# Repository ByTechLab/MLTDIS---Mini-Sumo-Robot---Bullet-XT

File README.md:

<div align="center">
    
</div>

Mini sumo robot - Bullet XT.

### Read more at BYTECHLAB:

<table style="width: 100%; border: none;" cellspacing="0" cellpadding="0" border="0">
  <tr>
    <td></td>
    <td>https://bytechlab.com/2017/09/minisumo-bullet-xt/</td>
  </tr>
</table>

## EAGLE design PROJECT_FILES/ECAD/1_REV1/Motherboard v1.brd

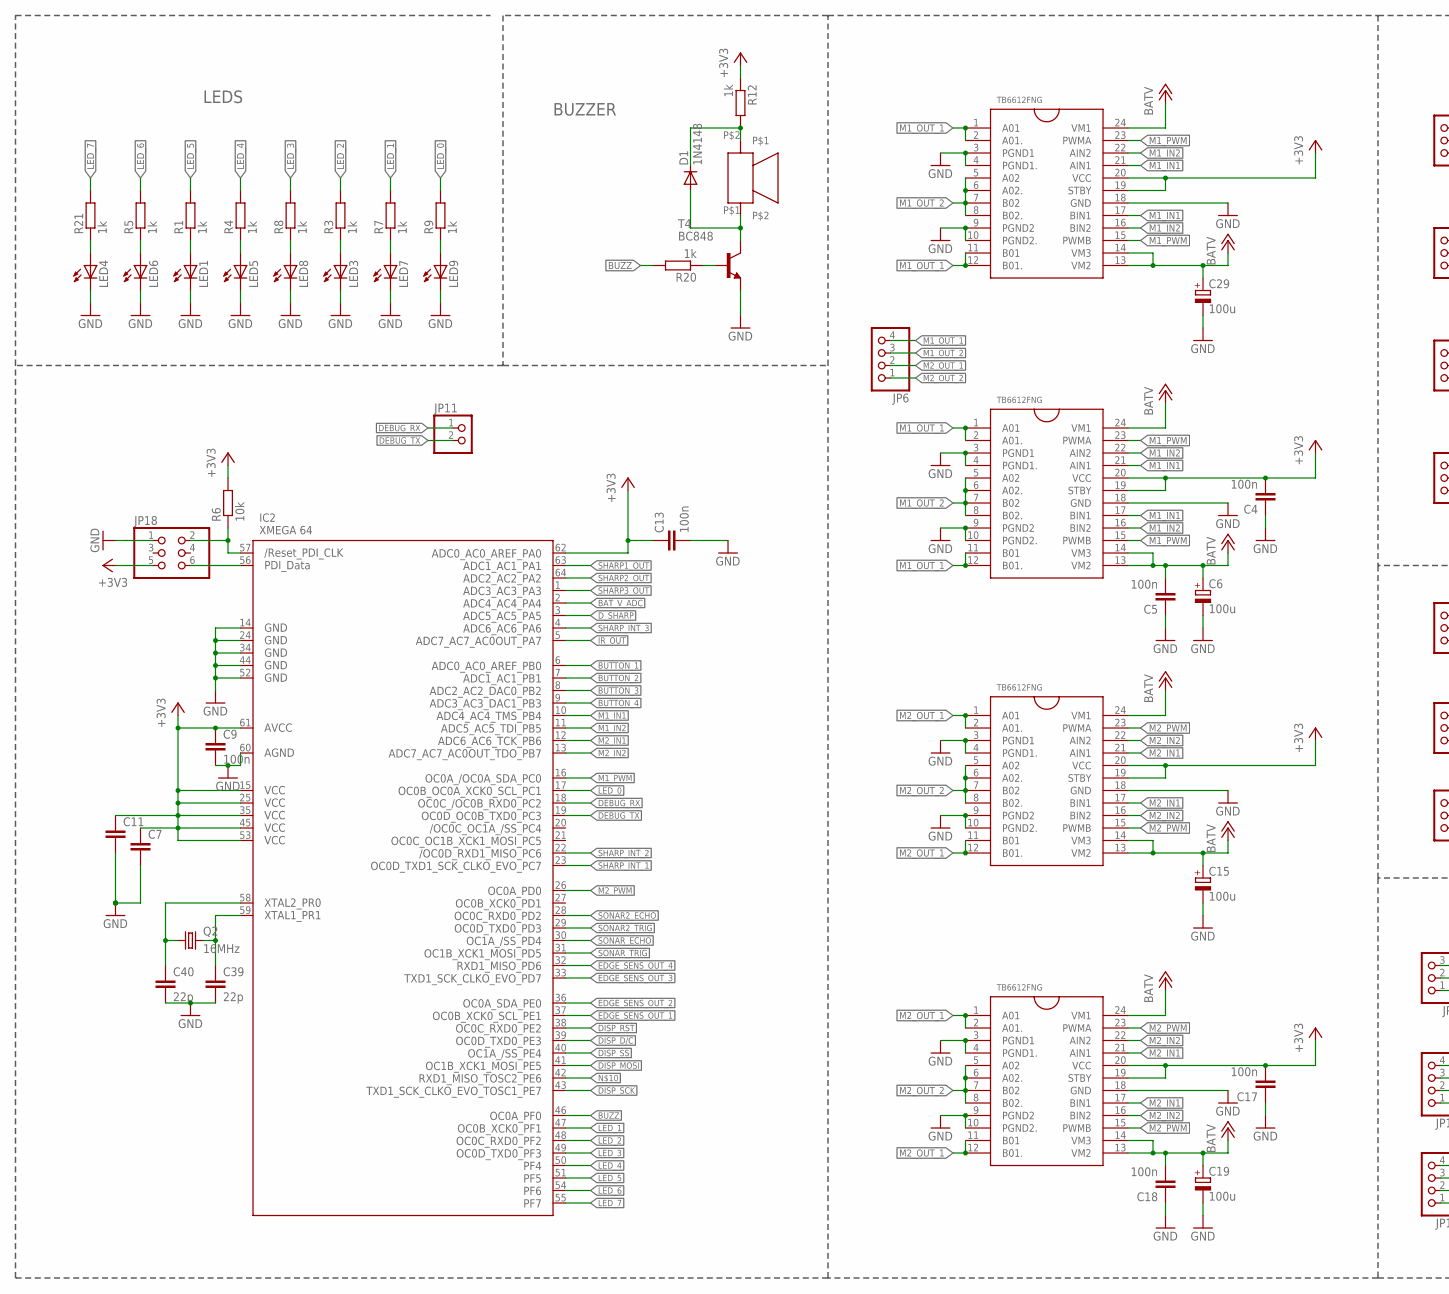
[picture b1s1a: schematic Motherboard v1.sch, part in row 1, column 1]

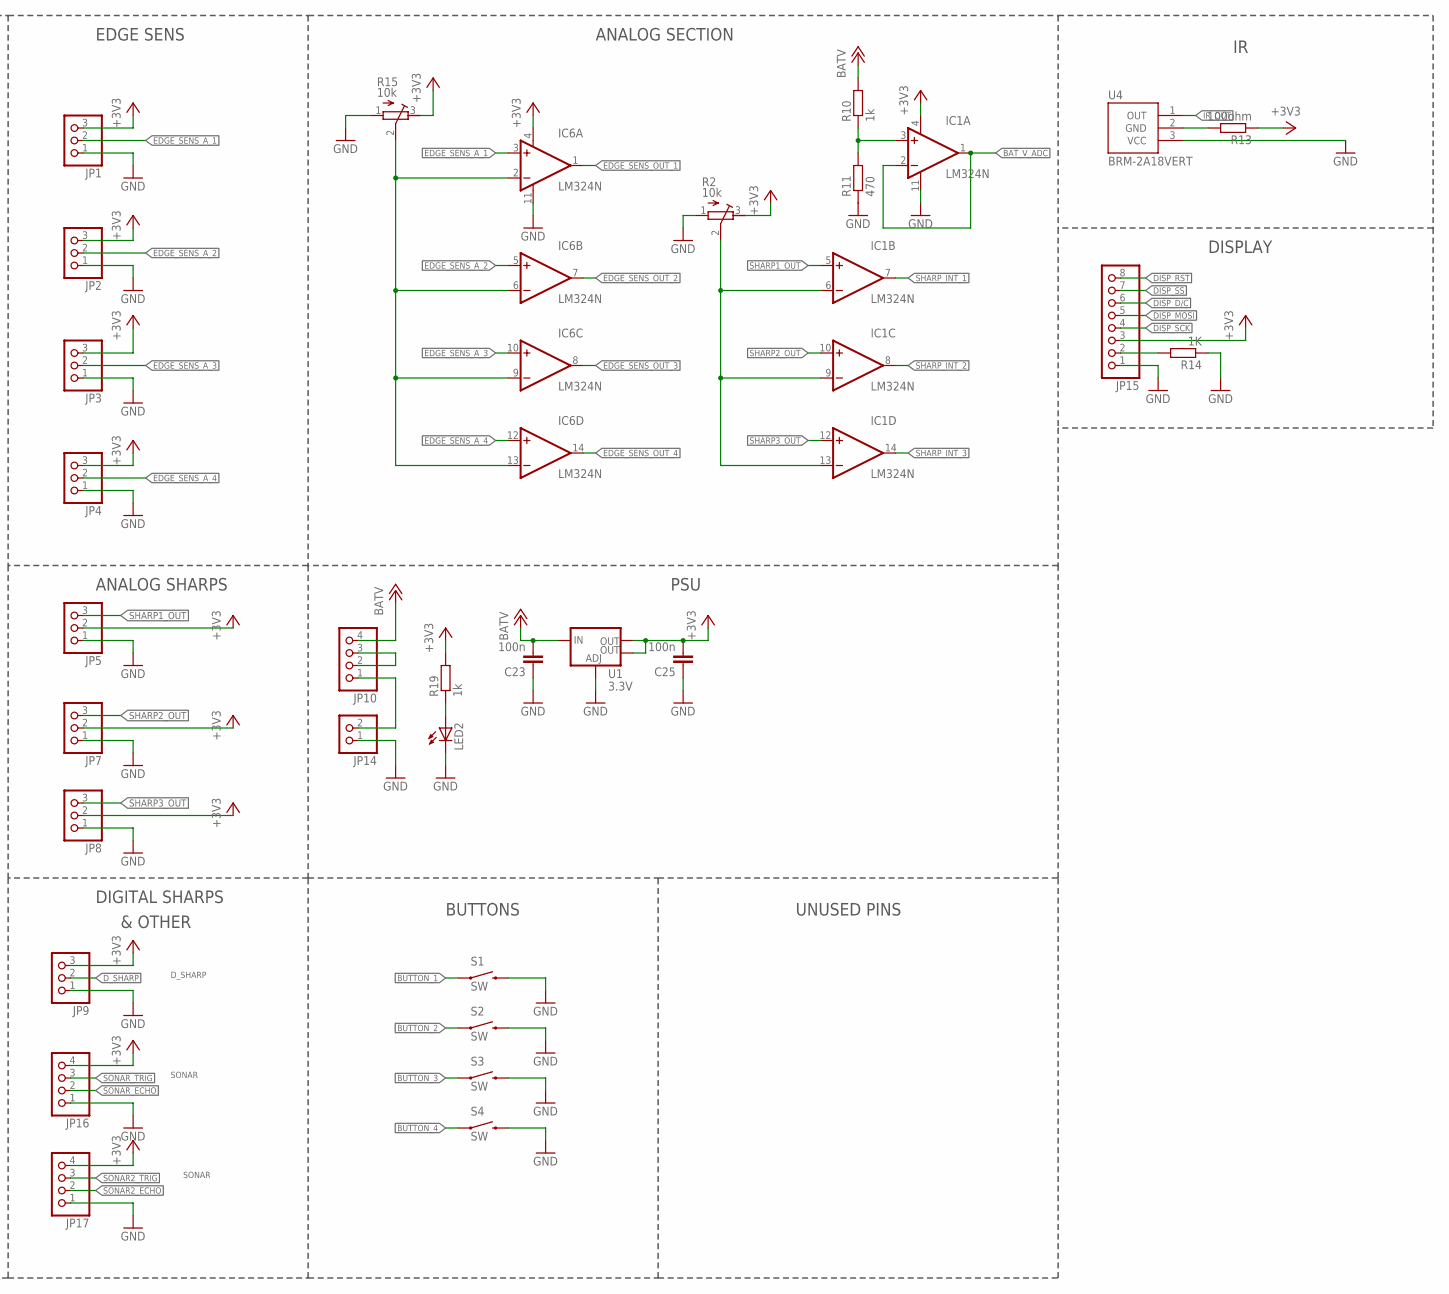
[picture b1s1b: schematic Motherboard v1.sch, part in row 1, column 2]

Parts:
C4, C5, C9, C13, C17, C18, C23, C25: 100n; C1206
C6, C15, C19, C29: 100u; 153CLV-0605
C7, C11: C-EUC1206; C1206
C39, C40: 22p; C1206
D1: 1N4148; SMB
IC1: LM324N; SO14; MPN OPA4130UA
IC2: XMEGA 64; TQFP64
IC6: LM324N; SO14
JP1, JP2, JP3, JP4, JP5, JP7, JP8, JP9: PINHD-1X3; 1X03
JP6, JP10: PINHD-1X4/90; 1X04/90
JP11, JP14: PINHD-1X2; 1X02
JP15: PINHD-1X8; 1X08
JP16, JP17: PINHD-1X4; 1X04
JP18: PINHD-2X3; 2X03
LED1, LED2, LED3, LED4, LED5, LED7, LED9: LEDCHIPLED_0805; CHIPLED_0805
LED6, LED8: LEDCHIP-LED0805; CHIP-LED0805
Q2: 16MHz; CSM-7X-DU
R1, R3, R4, R5, R7, R8, R9, R10, R12, R19, R20, R21: 1k; R1206
R2, R15: 10k; RTRIMTSM53YL
R6: 10k; R1206
R11: 470; R1206
R13: 100ohm; R1206
R14: 1K; R1206
S1, S2, S3, S4: SW; TACTILE-SWITCH-1101NE
T4: BC848; SOT23
U1: 3.3V; SOT223
U4: BRM-2A18VERT; BRM-2508_VERT
U$1, U$2, U$3, U$4: TB6612FNG; SSOP24
U$13: BOT-03; BOT-03D

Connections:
+3V3: C4.2, C7.1, C9.1, C11.1, C13.1, C17.2, C25.2, IC1.4 (V+), IC2.15 (VCC1), IC2.25 (VCC2), IC2.35 (VCC3), IC2.45 (VCC4), IC2.53 (VCC5), IC2.61 (AVCC), IC2.62 (PA0), IC6.4 (V+), JP1.3, JP2.3, JP3.3, JP4.3, JP5.2, JP7.2, JP8.2, JP9.3, JP15.3, JP16.4, JP17.4, JP18.5, R2.3 (E), R6.2, R12.1, R13.1, R15.3 (E), R19.2, U1.2 (OUT), U1.4 (OUT), U$1.19 (STBY), U$1.20 (VCC), U$2.19 (STBY), U$2.20 (VCC), U$3.19 (STBY), U$3.20 (VCC), U$4.19 (STBY), U$4.20 (VCC)
+12V: C5.2, C6.+, C15.+, C18.2, C19.+, C23.2, C29.+, JP10.4, R10.2, U1.3 (IN), U$1.13 (VM2), U$1.14 (VM3), U$1.24 (VM1), U$2.13 (VM2), U$2.14 (VM3), U$2.24 (VM1), U$3.13 (VM2), U$3.14 (VM3), U$3.24 (VM1), U$4.13 (VM2), U$4.14 (VM3), U$4.24 (VM1)
BAT_V_ADC: IC1.1 (OUT), IC1.2 (-IN), IC2.2 (PA4)
BUTTON_1: IC2.6 (PB0), S1.1
BUTTON_2: IC2.7 (PB1), S2.1
BUTTON_3: IC2.8 (PB2), S3.1
BUTTON_4: IC2.9 (PB3), S4.1
BUZZ: IC2.46 (PF0), R20.2
DEBUG_RX: IC2.18 (PC2), JP11.1
DEBUG_TX: IC2.19 (PC3), JP11.2
DISP_D/C: IC2.39 (PE3), JP15.6
DISP_MOSI: IC2.41 (PE5), JP15.5
DISP_RST: IC2.38 (PE2), JP15.8
DISP_SCK: IC2.43 (PE7), JP15.4
DISP_SS: IC2.40 (PE4), JP15.7
D_SHARP: IC2.3 (PA5), JP9.2
EDGE_SENS_A_1: IC6.3 (+IN), JP1.2
EDGE_SENS_A_2: IC6.5 (+IN), JP2.2
EDGE_SENS_A_3: IC6.10 (+IN), JP3.2
EDGE_SENS_A_4: IC6.12 (+IN), JP4.2
EDGE_SENS_OUT_1: IC2.37 (PE1), IC6.1 (OUT)
EDGE_SENS_OUT_2: IC2.36 (PE0), IC6.7 (OUT)
EDGE_SENS_OUT_3: IC2.33 (PD7), IC6.8 (OUT)
EDGE_SENS_OUT_4: IC2.32 (PD6), IC6.14 (OUT)
GND: C4.1, C5.1, C6.-, C7.2, C9.2, C11.2, C13.2, C15.-, C17.1, C18.1, C19.-, C23.1, C25.1, C29.-, C39.2, C40.2, IC1.11 (V-), IC2.14 (GND1), IC2.24 (GND2), IC2.34 (GND3), IC2.44 (GND4), IC2.52 (GND5), IC2.60 (AGND), IC6.11 (V-), JP1.1, JP2.1, JP3.1, JP4.1, JP5.1, JP7.1, JP8.1, JP9.1, JP14.1, JP15.1, JP16.1, JP17.1, JP18.1, LED1.C, LED2.C, LED3.C, LED4.C, LED5.C, LED6.C, LED7.C, LED8.C, LED9.C, R2.1 (A), R11.1, R14.1, R15.1 (A), S1.2, S2.2, S3.2, S4.2, T4.2 (E), U1.1 (ADJ), U4.3 (VCC), U$1.3 (PGND1), U$1.4 (PGND1.), U$1.9 (PGND2), U$1.10 (PGND2.), U$1.18 (GND), U$2.3 (PGND1), U$2.4 (PGND1.), U$2.9 (PGND2), U$2.10 (PGND2.), U$2.18 (GND), U$3.3 (PGND1), U$3.4 (PGND1.), U$3.9 (PGND2), U$3.10 (PGND2.), U$3.18 (GND), U$4.3 (PGND1), U$4.4 (PGND1.), U$4.9 (PGND2), U$4.10 (PGND2.), U$4.18 (GND)
IR_OUT: IC2.5 (PA7), U4.1 (OUT)
LED_0: IC2.17 (PC1), R9.2
LED_1: IC2.47 (PF1), R7.2
LED_2: IC2.48 (PF2), R3.2
LED_3: IC2.49 (PF3), R8.2
LED_4: IC2.50 (PF4), R4.2
LED_5: IC2.51 (PF5), R1.2
LED_6: IC2.54 (PF6), R5.2
LED_7: IC2.55 (PF7), R21.2
M1_IN1: IC2.10 (PB4), U$1.17 (BIN1), U$1.21 (AIN1), U$2.17 (BIN1), U$2.21 (AIN1)
M1_IN2: IC2.11 (PB5), U$1.16 (BIN2), U$1.22 (AIN2), U$2.16 (BIN2), U$2.22 (AIN2)
M1_OUT_1: JP6.4, U$1.1 (A01), U$1.2 (A01.), U$1.11 (B01), U$1.12 (B01.), U$2.1 (A01), U$2.2 (A01.), U$2.11 (B01), U$2.12 (B01.)
M1_OUT_2: JP6.3, U$1.5 (A02), U$1.6 (A02.), U$1.7 (B02), U$1.8 (B02.), U$2.5 (A02), U$2.6 (A02.), U$2.7 (B02), U$2.8 (B02.)
M1_PWM: IC2.16 (PC0), U$1.15 (PWMB), U$1.23 (PWMA), U$2.15 (PWMB), U$2.23 (PWMA)
M2_IN1: IC2.12 (PB6), U$3.17 (BIN1), U$3.21 (AIN1), U$4.17 (BIN1), U$4.21 (AIN1)
M2_IN2: IC2.13 (PB7), U$3.16 (BIN2), U$3.22 (AIN2), U$4.16 (BIN2), U$4.22 (AIN2)
M2_OUT_1: JP6.2, U$3.1 (A01), U$3.2 (A01.), U$3.11 (B01), U$3.12 (B01.), U$4.1 (A01), U$4.2 (A01.), U$4.11 (B01), U$4.12 (B01.)
M2_OUT_2: JP6.1, U$3.5 (A02), U$3.6 (A02.), U$3.7 (B02), U$3.8 (B02.), U$4.5 (A02), U$4.6 (A02.), U$4.7 (B02), U$4.8 (B02.)
M2_PWM: IC2.26 (PD0), U$3.15 (PWMB), U$3.23 (PWMA), U$4.15 (PWMB), U$4.23 (PWMA)
unnamed: LED1.A, R1.1
unnamed: LED5.A, R4.1
unnamed: LED6.A, R5.1
unnamed: LED3.A, R3.1
unnamed: LED7.A, R7.1
unnamed: LED8.A, R8.1
unnamed: LED9.A, R9.1
unnamed: R13.2, U4.2 (GND)
unnamed: JP10.2, JP10.3
unnamed: D1.C, R12.2, U$13.P$2
unnamed: IC2.56 (PDI_DATA), JP18.6
unnamed: IC2.57 (RESET), JP18.2, R6.1
unnamed: JP10.1, JP14.2
unnamed: IC1.6 (-IN), IC1.9 (-IN), IC1.13 (-IN), R2.2 (S)
unnamed: D1.A, T4.3 (C), U$13.P$1
unnamed: R20.1, T4.1 (B)
unnamed: IC6.2 (-IN), IC6.6 (-IN), IC6.9 (-IN), IC6.13 (-IN), R15.2 (S)
unnamed: JP15.2, R14.2
unnamed: IC1.3 (+IN), R10.1, R11.2
unnamed: C40.1, IC2.58 (PR0), Q2.1
unnamed: C39.1, IC2.59 (PR1), Q2.2
unnamed: LED2.A, R19.1
unnamed: LED4.A, R21.1
SHARP1_OUT: IC1.5 (+IN), IC2.63 (PA1), JP5.3
SHARP2_OUT: IC1.10 (+IN), IC2.64 (PA2), JP7.3
SHARP3_OUT: IC1.12 (+IN), IC2.1 (PA3), JP8.3
SHARP_INT_1: IC1.7 (OUT), IC2.23 (PC7)
SHARP_INT_2: IC1.8 (OUT), IC2.22 (PC6)
SHARP_INT_3: IC1.14 (OUT), IC2.4 (PA6)
SONAR2_ECHO: IC2.28 (PD2), JP17.2
SONAR2_TRIG: IC2.29 (PD3), JP17.3
SONAR_ECHO: IC2.30 (PD4), JP16.2
SONAR_TRIG: IC2.31 (PD5), JP16.3

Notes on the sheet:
LEDS
BUZZER
EDGE SENS
ANALOG SHARPS
DIGITAL SHARPS
& OTHER
PSU
BUTTONS
UNUSED PINS
DISPLAY
ANALOG SECTION
SONAR
D_SHARP

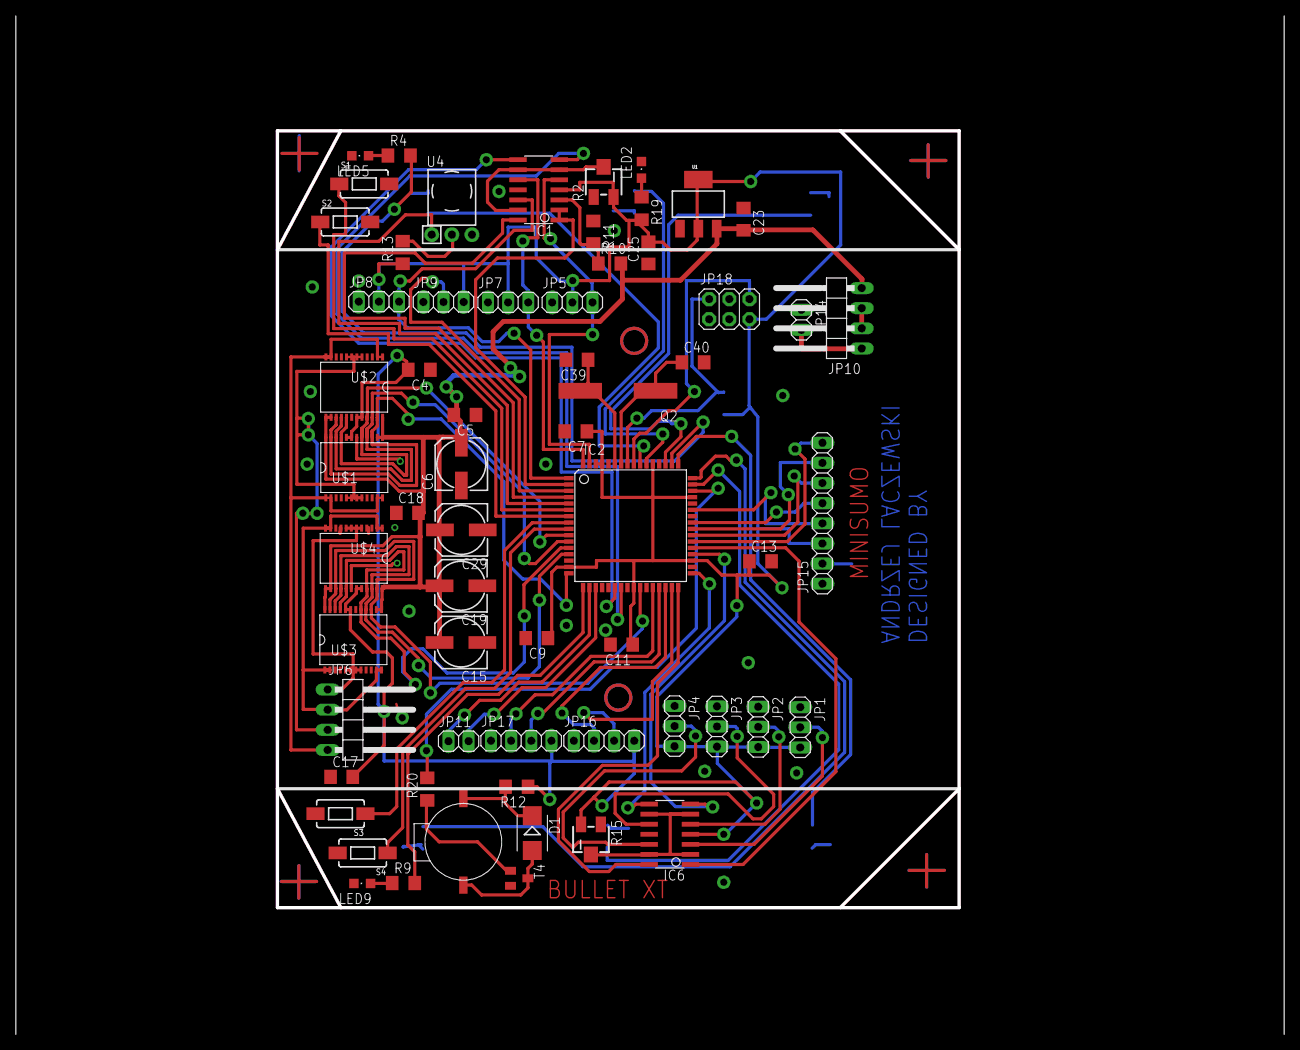
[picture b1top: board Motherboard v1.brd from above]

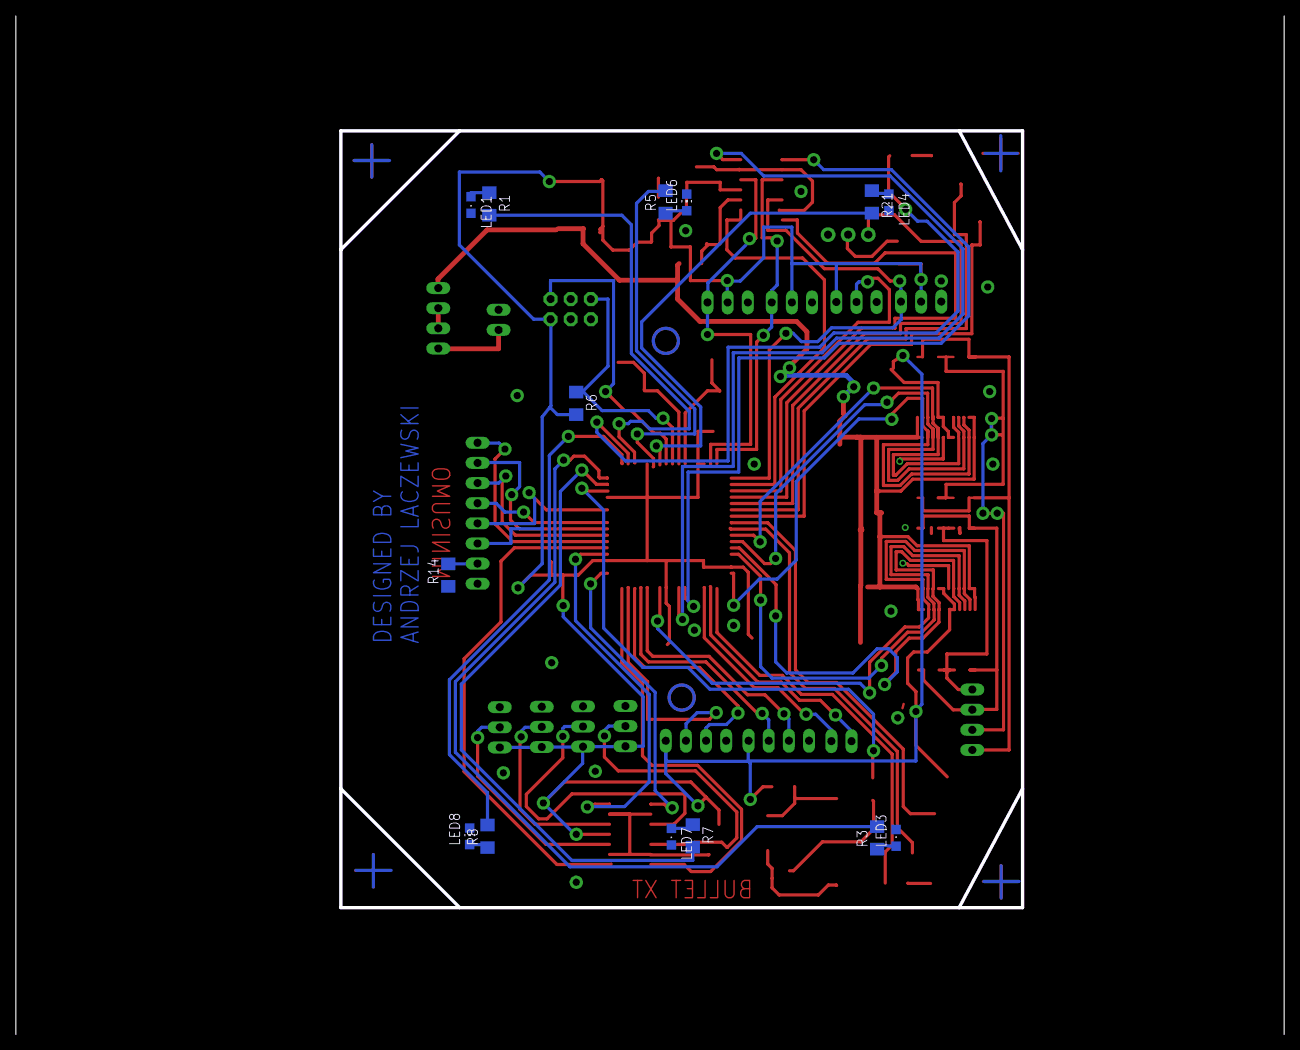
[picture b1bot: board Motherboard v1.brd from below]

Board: 2 copper layers, 86.0 x 98.0 mm, 76 parts (14 on the bottom side), 77 nets.

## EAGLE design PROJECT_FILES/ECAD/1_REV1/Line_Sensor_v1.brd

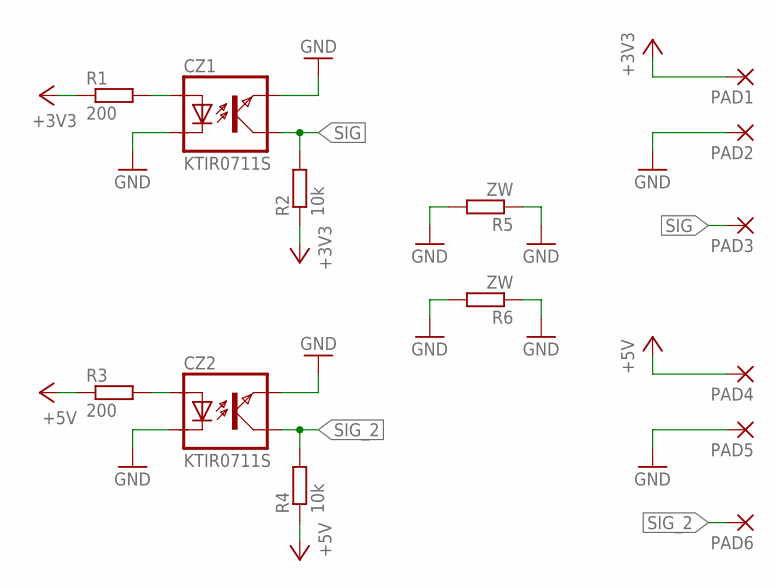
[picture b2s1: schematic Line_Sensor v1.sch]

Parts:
CZ1, CZ2: KTIR0711S; TOP
PAD1, PAD2, PAD3, PAD4, PAD5, PAD6: SMD5; SMD2,54-5,08
R1, R3: 200; R1206
R2, R4: 10k; R1206
R5, R6: ZW; R1206

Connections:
+3V3: PAD1.1, R1.1, R2.1
+5V: PAD4.1, R3.1, R4.1
GND: CZ1.EMITER, CZ1.KATODA, CZ2.EMITER, CZ2.KATODA, PAD2.1, PAD5.1, R5.1, R5.2, R6.1, R6.2
unnamed: CZ1.ANODA, R1.2
unnamed: CZ2.ANODA, R3.2
SIG: CZ1.KOLEKTOR, PAD3.1, R2.2
SIG_2: CZ2.KOLEKTOR, PAD6.1, R4.2

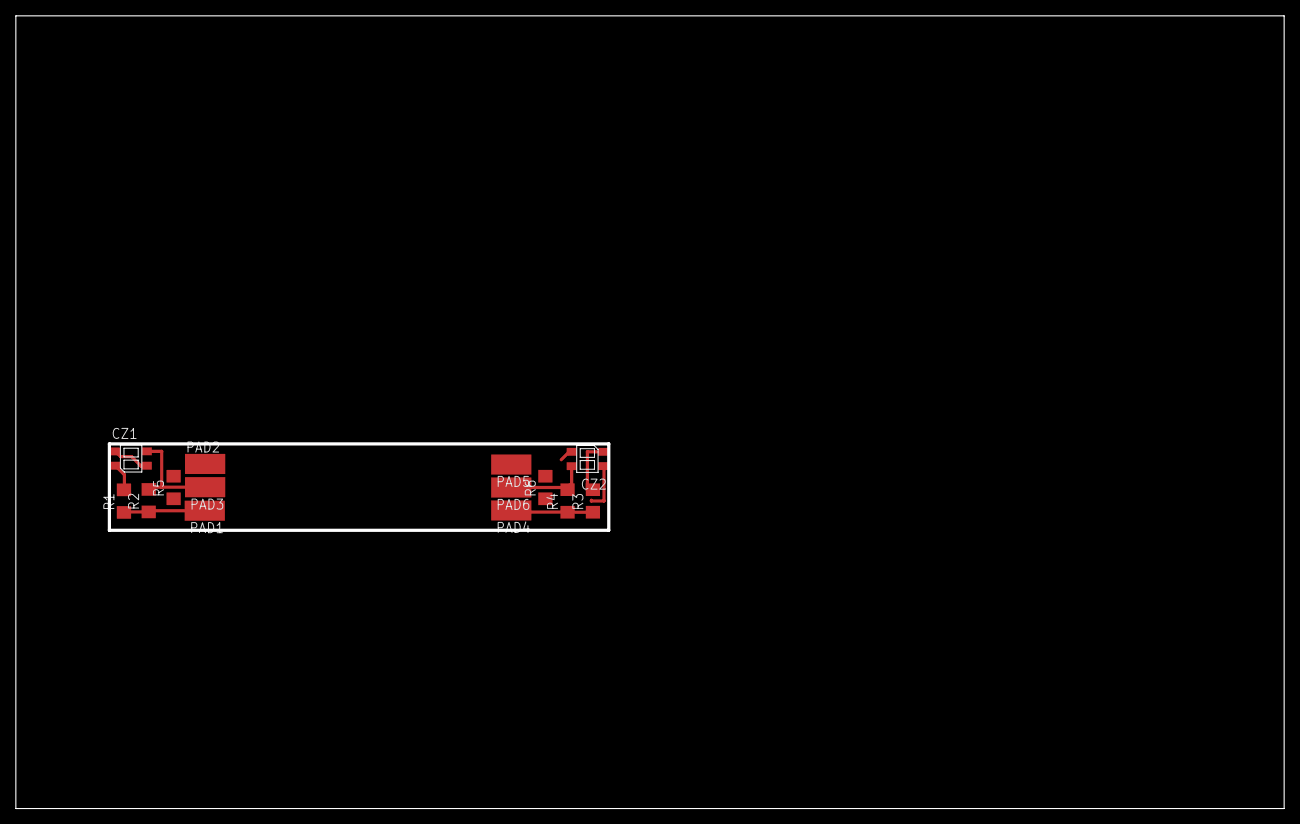
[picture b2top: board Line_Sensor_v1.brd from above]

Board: 2 copper layers, 160.0 x 100.0 mm, 14 parts (0 on the bottom side), 7 nets.

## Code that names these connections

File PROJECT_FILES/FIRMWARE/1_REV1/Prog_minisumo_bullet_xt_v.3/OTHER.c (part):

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	PORTA.DIRCLR = PIN3_bm;//PIN3 --> ADC  SHARP 3
	PORTA.DIRCLR = PIN4_bm;//PIN4 --> ADC BAT VOLTAGE
	PORTA.DIRCLR = PIN5_bm;//PIN5 --> DIGITAL SHARP
	PORTA.DIRCLR = PIN6_bm;//PIN6 --> SHARP_INT_3
	PORTA.PIN6CTRL  =    PORT_ISC_RISING_gc;
	PORTA.INT0MASK  =    PIN6_bm;
	PORTA.PIN5CTRL  =    PORT_ISC_FALLING_gc;
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	PORTB.PIN2CTRL  =    PORT_OPC_PULLUP_gc;
	PORTB.PIN3CTRL  =    PORT_OPC_PULLUP_gc;
	
	PORTB.DIRSET = PIN4_bm;//PIN4 --> M1_IN1
	PORTB.DIRSET = PIN5_bm;//PIN5 --> M1_IN2
	PORTB.DIRSET = PIN6_bm;//PIN6 --> M2_IN1
	PORTB.DIRSET = PIN7_bm;//PIN7 --> M2_IN2
	/*----------------------END----ANALOG--------------------------*/
	// --------------PORTC--------------
	PORTC.DIRSET = PIN0_bm;//PIN0 -->M1 PWM
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	PORTC.DIRSET = PIN3_bm;//PIN3 -->DBG TX
	//PIN4 -->
	//PIN5 -->
	PORTC.DIRCLR = PIN6_bm;//PIN6 -->SHARP_INT_2
	PORTC.PIN6CTRL  =    PORT_ISC_RISING_gc;
	PORTC.INT0MASK  =    PIN6_bm;
	
	PORTC.DIRCLR = PIN7_bm;//PIN7 -->SHARP_INT_1
	PORTC.PIN7CTRL  =    PORT_ISC_RISING_gc;
	PORTC.INT1MASK  =    PIN7_bm;
	PORTC.INTCTRL   =    PORT_INT0LVL_MED_gc|PORT_INT1LVL_MED_gc;
	// --------------PORTD--------------
	PORTD.DIRSET = PIN0_bm;//PIN0 -->M2 PWM
	//PIN1 -->
	//PIN2 -->SONAR2_ECHO
	//PIN3 -->SONAR2_TRIG
	//PIN4 -->SONAR1_ECHO
	//PIN5 -->SONAR1_TRIG
	PORTD.DIRCLR = PIN6_bm;//PIN6 -->EDGE_SENS_4
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	PORTE.INT1MASK  =    PIN1_bm;
	PORTE.INTCTRL   =    PORT_INT0LVL_MED_gc|PORT_INT1LVL_MED_gc;
	
	PORTE.DIRSET    =    PIN2_bm;//PIN2 -->DISP_RST
	PORTE.DIRSET    =    PIN3_bm;//PIN3 -->DISP_D/C
	PORTE.DIRSET    =    PIN4_bm;//PIN4 -->DISP_SS
	PORTE.DIRSET    =    PIN5_bm;//PIN5 -->DISP_MOSI
	//PIN6 -->
	PORTE.DIRSET    =    PIN7_bm;//PIN7 -->DISP_SCK
	// --------------PORTF--------------
	PORTF.DIRSET    =    PIN0_bm; // BUZZER
	PORTF.DIRSET    =    PIN1_bm; // LED
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
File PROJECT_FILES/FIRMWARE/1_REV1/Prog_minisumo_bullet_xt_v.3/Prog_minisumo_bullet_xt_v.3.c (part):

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	SENS_FLAG_s.SHARP_DIGIT=1;
}
ISR(TCE0_OVF_vect) {		//button sense interupt 4ms
	if (BUTTON_status(BUTTON_1_CHECK,BUTTON_1)==BUTTON_RISING_EDGE) BTN_s._1=1;
	if (BUTTON_status(BUTTON_2_CHECK,BUTTON_2)==BUTTON_RISING_EDGE) BTN_s._2=1;
	if (BUTTON_status(BUTTON_3_CHECK,BUTTON_3)==BUTTON_RISING_EDGE) BTN_s._3=1;
	if (BUTTON_status(BUTTON_4_CHECK,BUTTON_4)==BUTTON_RISING_EDGE) BTN_s._4=1;
	
	if (BUZZER_DELAY_TICK == 0) BUZZ_OFF;
	if (BUZZER_DELAY_TICK > 0)BUZZER_DELAY_TICK--;
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
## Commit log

2024-11-24 Upload project files
2025-08-17 Uplaod files

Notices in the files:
parts and their libraries:
SparkFun-PowerIC: Licensing: Creative Commons ShareAlike 4.0 International - https://creativecommons.org/licenses/by-sa/4.0
